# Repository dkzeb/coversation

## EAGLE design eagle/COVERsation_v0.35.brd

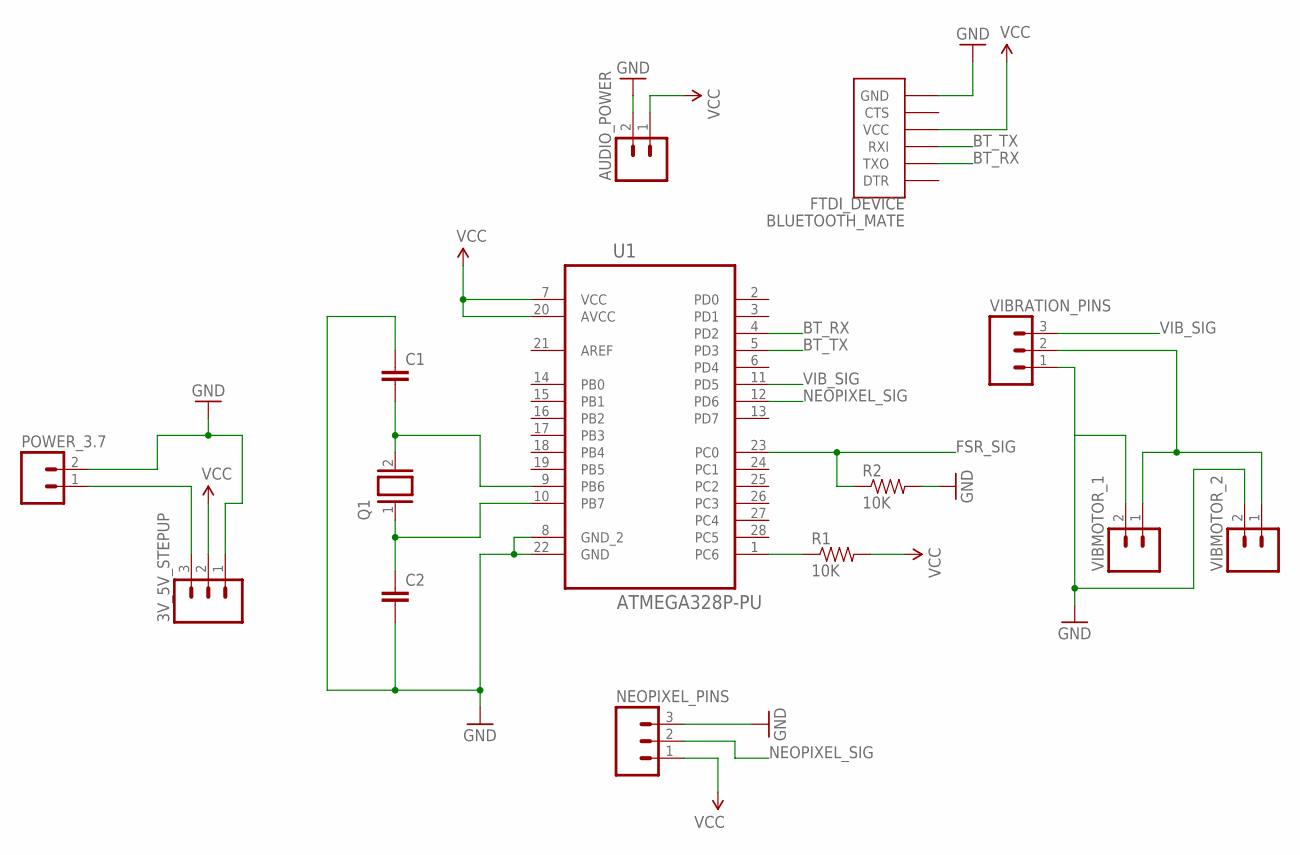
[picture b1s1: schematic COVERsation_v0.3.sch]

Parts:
3V_5V_STEPUP: M03PTH; 1X03
AUDIO_POWER: M02PTH; 1X02
BLUETOOTH_MATE: FTDI_DEVICE; FTDI_DEVICE_SIDE
C1, C2: CAPPTH1; CAP-PTH-5MM
NEOPIXEL_PINS: M03PTH; 1X03
POWER_3.7: M02PTH; 1X02
Q1: XTAL; Q
R1, R2: 10K; AXIAL-0.3EZ
U1: ATMEGA328P-PU; DIP254P762X457-28
VIBMOTOR_1, VIBMOTOR_2: M02PTH; 1X02
VIBRATION_PINS: M03PTH; 1X03

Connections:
BT_RX: BLUETOOTH_MATE.P$2 (TXO), U1.4 (PD2)
BT_TX: BLUETOOTH_MATE.P$3 (RXI), U1.5 (PD3)
FSR_SIG: R2.P$1 (1), U1.23 (PC0)
GND: 3V_5V_STEPUP.1, AUDIO_POWER.2, BLUETOOTH_MATE.P$6 (GND), C1.1, C2.2, NEOPIXEL_PINS.3, POWER_3.7.2, R2.P$2 (2), U1.8 (GND_2), U1.22 (GND), VIBMOTOR_1.2, VIBMOTOR_2.2, VIBRATION_PINS.1
unnamed: C1.2, Q1.2, U1.9 (PB6)
unnamed: C2.1, Q1.1, U1.10 (PB7)
unnamed: 3V_5V_STEPUP.3, POWER_3.7.1
unnamed: R1.P$1 (1), U1.1 (PC6)
unnamed: VIBMOTOR_1.1, VIBMOTOR_2.1, VIBRATION_PINS.2
NEOPIXEL_SIG: NEOPIXEL_PINS.2, U1.12 (PD6)
VCC: 3V_5V_STEPUP.2, AUDIO_POWER.1, BLUETOOTH_MATE.P$4 (VCC), NEOPIXEL_PINS.1, R1.P$2 (2), U1.7 (VCC), U1.20 (AVCC)
VIB_SIG: U1.11 (PD5), VIBRATION_PINS.3

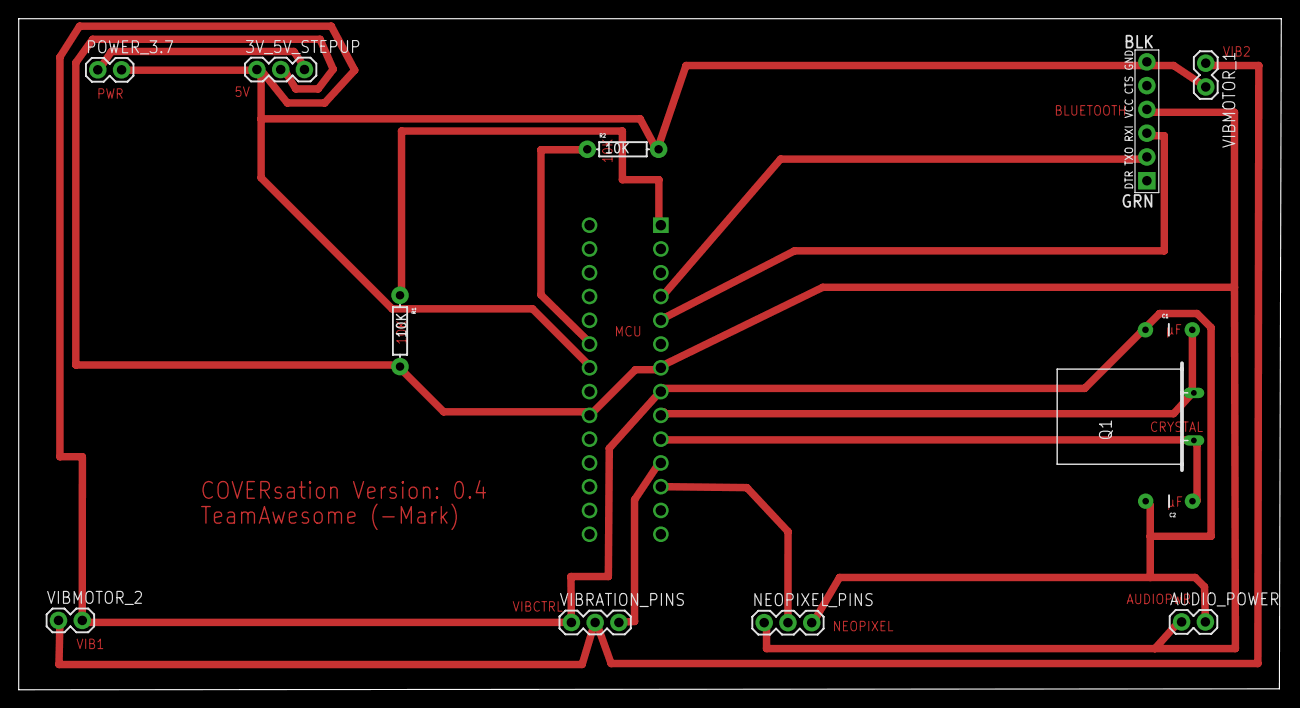
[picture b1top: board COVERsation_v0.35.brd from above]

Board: 2 copper layers, 134.9 x 71.7 mm, 14 parts (1 on the bottom side), 12 nets.

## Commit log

2016-10-12 Arduino Code
2016-10-12 Android and Eagle files

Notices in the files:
parts and their libraries:
SparkFun-Aesthetics: Licensing: Creative Commons ShareAlike 4.0 International - https://creativecommons.org/licenses/by-sa/4.0
